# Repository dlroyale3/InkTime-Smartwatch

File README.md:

# Proiect InkTime - E-Paper Smartwatch (nRF52840)

## Descriere Generală
InkTime este un prototip hardware de smartwatch (dispozitiv wearable) proiectat de la zero, cu un focus absolut pe eficiența energetică (Ultra-Low Power) și miniaturizare. 
Creierul sistemului este SoC-ul **Nordic nRF52840**, capabil de conectivitate Bluetooth 5.0 LE. Dispozitivul interacționează cu utilizatorul printr-un ecran E-Paper de 3.3V (tehnologie bistabilă), butoane tactile și feedback haptic (motor liniar/ERM), fiind capabil să monitorizeze activitatea fizică prin intermediul unui accelerometru integrat.

---

## 1. Diagramă Bloc

Arhitectura hardware este centrată în jurul microcontrolerului, care acționează ca un Master I2C/SPI pentru toate perifericele, permițând controlul granular al stărilor de alimentare pentru fiecare modul în parte.

---

## 2. Bill of Materials (BOM) - Componente Principale

Pentru producția și asamblarea PCB-ului (PCBA), componentele au fost selectate pe baza disponibilității la producătorul JLCPCB (LCSC Parts) și a footprint-ului redus (QFN, BGA sau 0402/0201 pentru pasive).

| Componentă (Designator) | Rol în Sistem | Producător | Datasheet | Link JLCPCB |
| :--- | :--- | :--- | :--- | :--- |
| **nRF52840-QIAA** (U1) | Microcontroller & BLE Radio | Nordic Semi | [Datasheet](https://infocenter.nordicsemi.com/pdf/nRF52840_PS_v1.7.pdf) | [C145322](https://jlcpcb.com/partdetail/NordicSemicon-nRF52840QIAAR/C145322) |
| **BQ25180YBGR** (IC1) | LiPo Battery Charger | Texas Instruments | [Datasheet](https://www.ti.com/lit/ds/symlink/bq25180.pdf) | [C3166611](https://jlcpcb.com/partdetail/TexasInstruments-BQ25180YBGR/C3166611) |
| **MAX17048G+T10** (U3) | Fuel Gauge (Monitor Baterie) | Analog Devices | [Datasheet](https://www.analog.com/media/en/technical-documentation/data-sheets/MAX17048-MAX17049.pdf) | [C82806](https://jlcpcb.com/partdetail/Maxim_Integrated-MAX17048GT10/C82806) |
| **RT6160AWSC** (IC9) | DC/DC Buck-Boost Converter | Richtek | [Datasheet](https://www.richtek.com/assets/product_file/RT6160A/DS6160A-02.pdf) | [C2834316](https://jlcpcb.com/parts) |
| **BMA423 / BMA421** (IC3) | Accelerometru Triaxial (IMU) | Bosch Sensortec | [Datasheet](https://www.bosch-sensortec.com/media/boschsensortec/downloads/datasheets/bst-bma423-ds004.pdf) | [C283838](https://jlcpcb.com/partdetail/BoschSensortec-BMA423/C283838) |
| **DRV2605YZFR** (IC2) | Haptic Driver (LRA/ERM) | Texas Instruments | [Datasheet](https://www.ti.com/lit/ds/symlink/drv2605.pdf) | [C74431](https://jlcpcb.com/partdetail/TexasInstruments-DRV2605YZFR/C74431) |
| **2450AT18B100E** (ANT1)| Antenă Ceramică 2.4 GHz | Johanson Tech | [Datasheet](https://www.johansontechnology.com/datasheets/2450AT18B100/2450AT18B100.pdf) | [C210086](https://jlcpcb.com/partdetail/JohansonTechnology-2450AT18B100E/C210086) |

*(Notă: Componentele pasive - rezistențe și condensatori de 0201/0402, inductoarele de putere și conectorii USB-C/FPC se regăsesc detaliate în fișierul `BOM.csv` din folderul Manufacturing).*

---

## 3. Funcționalitate Hardware Detaliată

Sistemul a fost împărțit în mai multe subsisteme, optimizate pentru a permite oprirea alimentării (Power Gating) atunci când nu sunt utilizate.

### 3.1. Procesare și Radio (nRF52840)
MCU-ul rulează la o tensiune stabilizată de 3.3V. Pentru a menține timing-ul BLE și RTC-ul (Real Time Clock) cu un consum de doar ~1.5µA, a fost integrat un cristal extern de 32.768 kHz (`X2`). Conexiunea radio se face printr-o rețea Pi-Matching către antena ceramică de 2.4GHz.

### 3.2. Magistrala I2C și Senzorii
Toate perifericele de monitorizare și input folosesc o magistrală comună **I2C** (Fast Mode - 400kHz), echipată cu rezistențe de pull-up de 10kΩ.
* **BMA423 (IMU - 0x18):** Configurabil să ruleze algoritmul de *step-counting* intern. Nu ține MCU-ul treaz; trimite un semnal pe pinul `IMU_INT1` doar când detectează pași sau gesturi (Tilt-to-Wake).
* **MAX17048 (Fuel Gauge - 0x36):** Estimează starea bateriei (State of Charge) fără a necesita o rezistență de șunt (care ar irosi energie), folosind algoritmul ModelGauge. Poate genera o alertă hardware (`ALERT`) când bateria scade sub un prag definit.
* **BQ25180 (Charger - 0x6A):** Negociază curentul de încărcare tras din portul USB-C (limitat software la 100mA - 300mA pentru a proteja celula LiPo mică).
* **DRV2605 (Haptic - 0x5A):** Conține o bibliotecă internă de forme de undă pentru vibrații. Este ținut în shutdown (consum <1µA) și activat doar la notificări prin pinul `HAPTIC_EN`.

### 3.3. Display-ul E-Paper (SPI)
Interfața vizuală folosește un panou bistabil conectat printr-un cablu FPC 24-pin.
* **Comunicația:** Se face via **SPI 4-wire** (doar TX/MOSI, deoarece ecranul nu trimite date înapoi, ci folosește un pin dedicat `EPD_BUSY` pentru a semnaliza starea).
* **Boost Circuit:** Deoarece cerneala electronică necesită tensiuni mari (VGH, VGL, +/- 15V) pentru a muta pigmenții, placa include circuitul de switching cu inductor de 68uH și diode Schottky MBR0530. Acest circuit este pornit exclusiv în secunda în care ecranul își dă refresh.

### 3.4. Calcule de Consum de Energie (Power Budget)
Eficiența proiectului se bazează pe regimul de funcționare *Duty-Cycled*. Estimarea autonomiei cu o baterie LiPo de **150 mAh**:

1. **Modul Deep Sleep (98% din timp):**
   * nRF52840 (System ON, RTC): ~1.5 µA
   * BMA423 (Low-power sensing): ~4 µA
   * BQ25180 + RT6160 (Quiescent): ~8 µA
   * Fuel Gauge (Hibernate): ~3 µA
   * Ecran E-Paper: 0 µA
   * **Total Sleep:** **~16.5 µA**

2. **Modul Activ (Evenimente periodice):**
   * Refresh Ecran (1 dată pe minut): ~8 mA timp de 1s.
   * Transmisie BLE: ~5 mA timp de 10ms.
   * **Consum Mediu Echivalent:** **~1.2 mA / oră** (incluzând spike-urile de refresh).

3. **Autonomie Teoretică:** `150 mAh / 1.2 mA ≈ 125 de ore (aprox. 5 zile)` de utilizare normală, cu potențial de extindere până la **săptămâni** dacă ecranul este actualizat doar la cerere (button press).

---

## 4. Alocarea Pinilor nRF52840 și Justificare

Rutarea pinilor (Pin Muxing) a fost aleasă strategic pentru a evita încrucișările pe PCB și pentru a grupa interfețele de mare viteză.

| Pin MCU | Funcție Atribuită | Tip Interfață | Justificarea Alegerii (Hardware Design) |
| :--- | :--- | :--- | :--- |
| **P0.00 / P0.01** | `XL1` / `XL2` | Analog | Pini dedicați hardware exclusiv pentru cristalul LFXO (32.768kHz). |
| **P0.06 / P0.07** | `SDA` / `SCL` | I2C (TWIM) | Plasați convenabil pe latura de jos a IC-ului, rutare directă spre grupul de senzori (Bottom). |
| **P0.08 / P1.08** | `IMU_INT1` / `IMU_INT2`| GPIO (Interrupt) | Intrări cu capacitate de *Wake-up*, conectate direct la accelerometru. |
| **P0.02 / P0.03** | `SCK` / `MOSI` | SPI (SPIM) | Alocați pentru a minimiza distanța fizică a traseelor de mare viteză către conectorul FPC al ecranului (partea dreaptă a plăcii). |
| **P0.17** | `EPD_BUSY` | GPIO (Input) | Citește flag-ul de busy de la ecran. Permite MCU-ului să doarmă între comenzile SPI. |
| **P1.06** | `HAPTIC_EN` | GPIO (Output) | Semnal digital simplu (Enable) pentru a tăia alimentarea driverului de vibrații. |
| **P1.01 / P1.02 / P1.03** | `SW_UP/DN/ENT` | GPIO (Input) | Pini configurați cu rezistențe de pull-up interne/externe pentru debounce-ul mecanic al butoanelor. |
| **SWDIO / SWDCLK** | Debug / Flash | SWD | Pini hardwired pentru programarea via conectorul TC2030-IDC. |

---

## 5. Design Log & PCB Layout (4-Layer Stackup)

PCB-ul a fost proiectat pe 4 straturi pentru a asigura plane solide de referință (GND), necesare disipării termice și integrității semnalului RF. 
S-a implementat o matrice de **Via Stitching** în jurul secțiunii de radiofrecvență și un decupaj (Polygon Cutout) pe toate cele 4 straturi sub antena Johanson, pentru a preveni atenuarea undelor electromagnetice.

* **Layer 1 (Top):** Găzduiește toate componentele SMD, planul de masă (GND) primar și traseele critice de scurtă distanță.

* **Layer 2 (Route2 / Inner GND):** Strat intern dedicat exclusiv unui plan de masă continuu (Solid Ground Plane). Acesta oferă o cale de întoarcere curată și scurtă pentru curenți, esențială pentru ecranarea zgomotului (EMI) și performanța antenei.

* **Layer 3 (Route63 / Inner Power):** Strat intern dedicat rețelelor de distribuție a puterii (`3V3`, `VBUS`, `VBAT`, `VREG`). Traseele au o lățime minimă de 0.3mm pentru a menține o impedanță redusă și a preveni căderile de tensiune la solicitări tranzitorii.

* **Layer 4 (Bottom):** Utilizat preponderent pentru rutarea magistralelor de date (ex: `I2C`) și pentru realizarea conexiunilor lungi care ar fi aglomerat fața Top. Dispune, de asemenea, de propriul plan de masă auxiliar.

### Testabilitate și Producție
Placa dispune de **Test Pad-uri** dedicate pentru toate semnalele critice (`3V3`, `VBAT`, `SDA`, `SCL`, `SWDIO`), etichetate clar pe layer-ul de Silkscreen, permițând depanarea facilă cu osciloscopul sau analizorul logic după asamblare.
### Testabilitate și Producție
Placa dispune de **Test Pad-uri** dedicate pentru toate semnalele critice (`3V3`, `VBAT`, `SDA`, `SCL`, `SWDIO`), etichetate clar pe layer-ul de Silkscreen, permițând depanarea facilă cu osciloscopul sau analizorul logic după asamblare.

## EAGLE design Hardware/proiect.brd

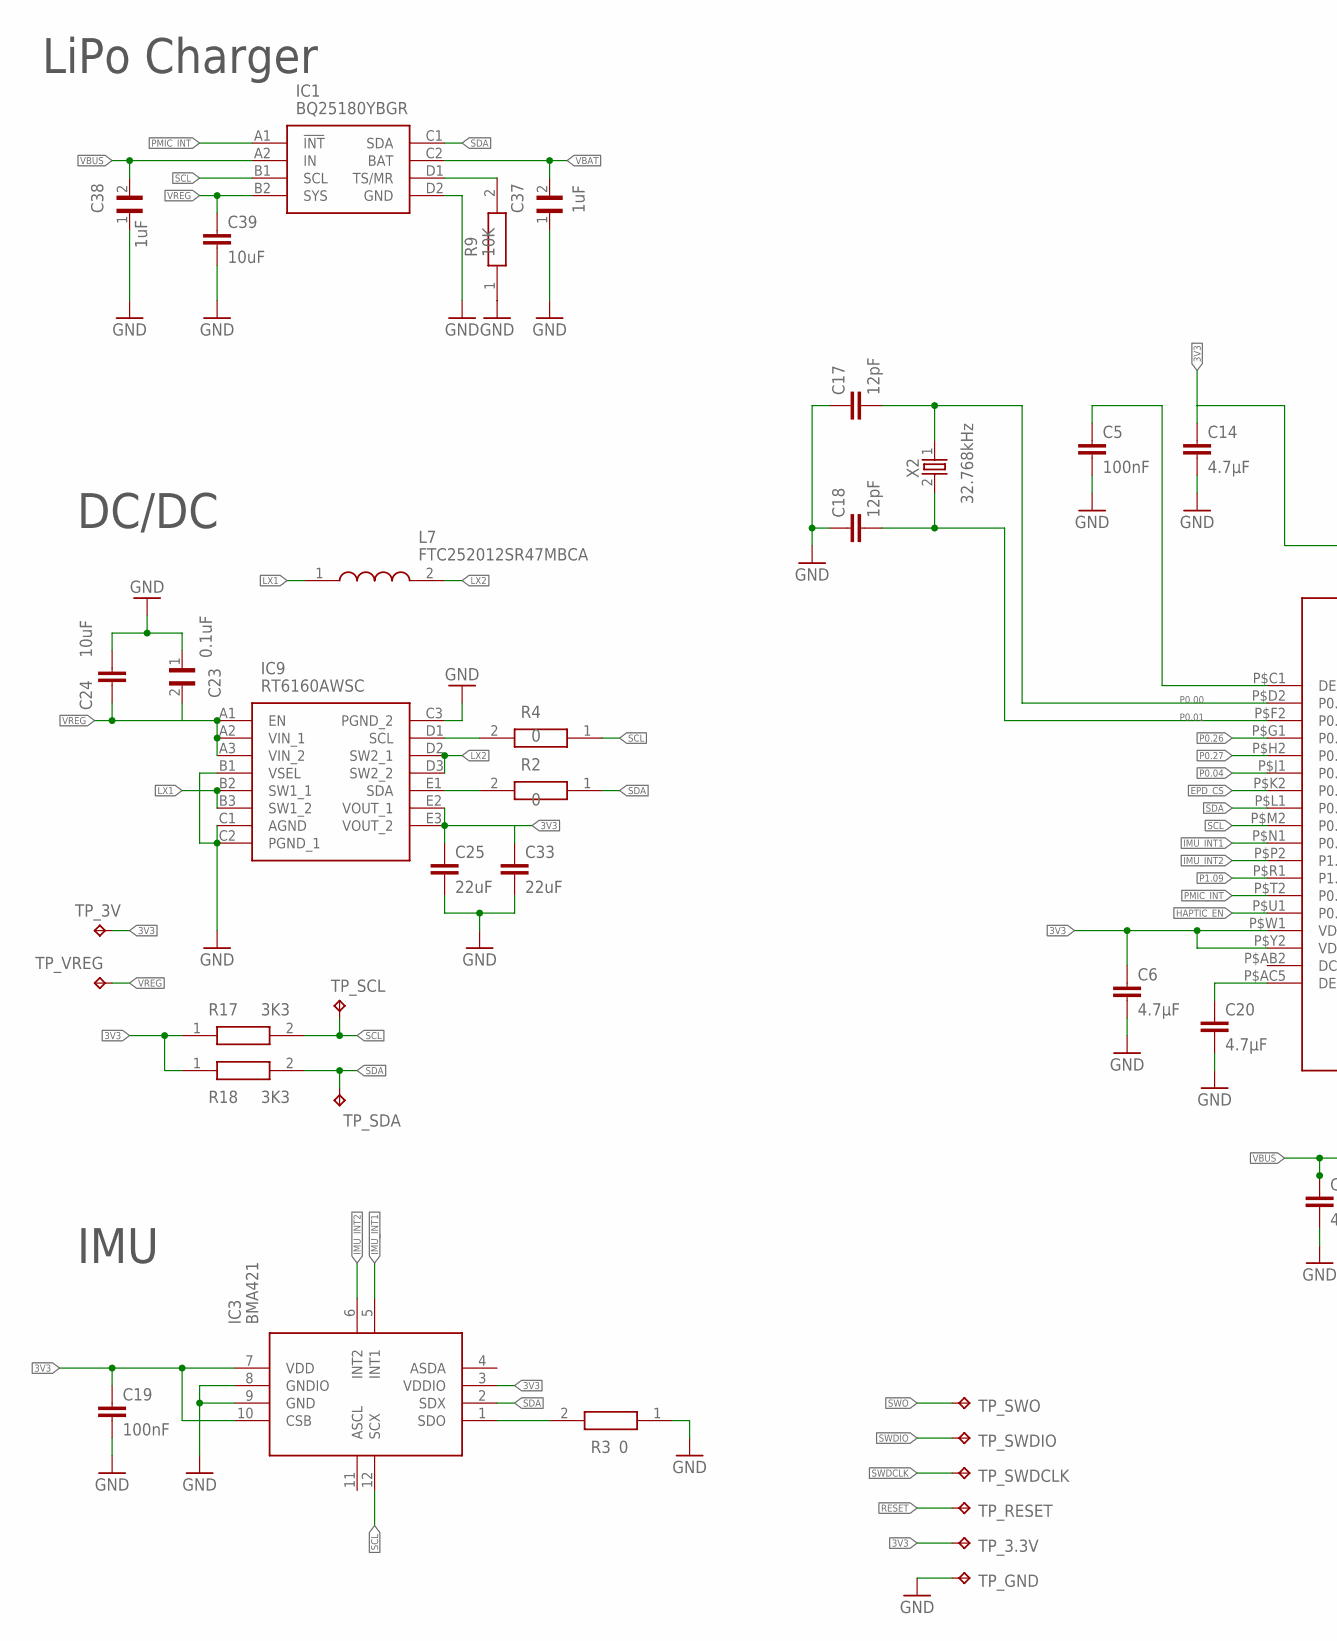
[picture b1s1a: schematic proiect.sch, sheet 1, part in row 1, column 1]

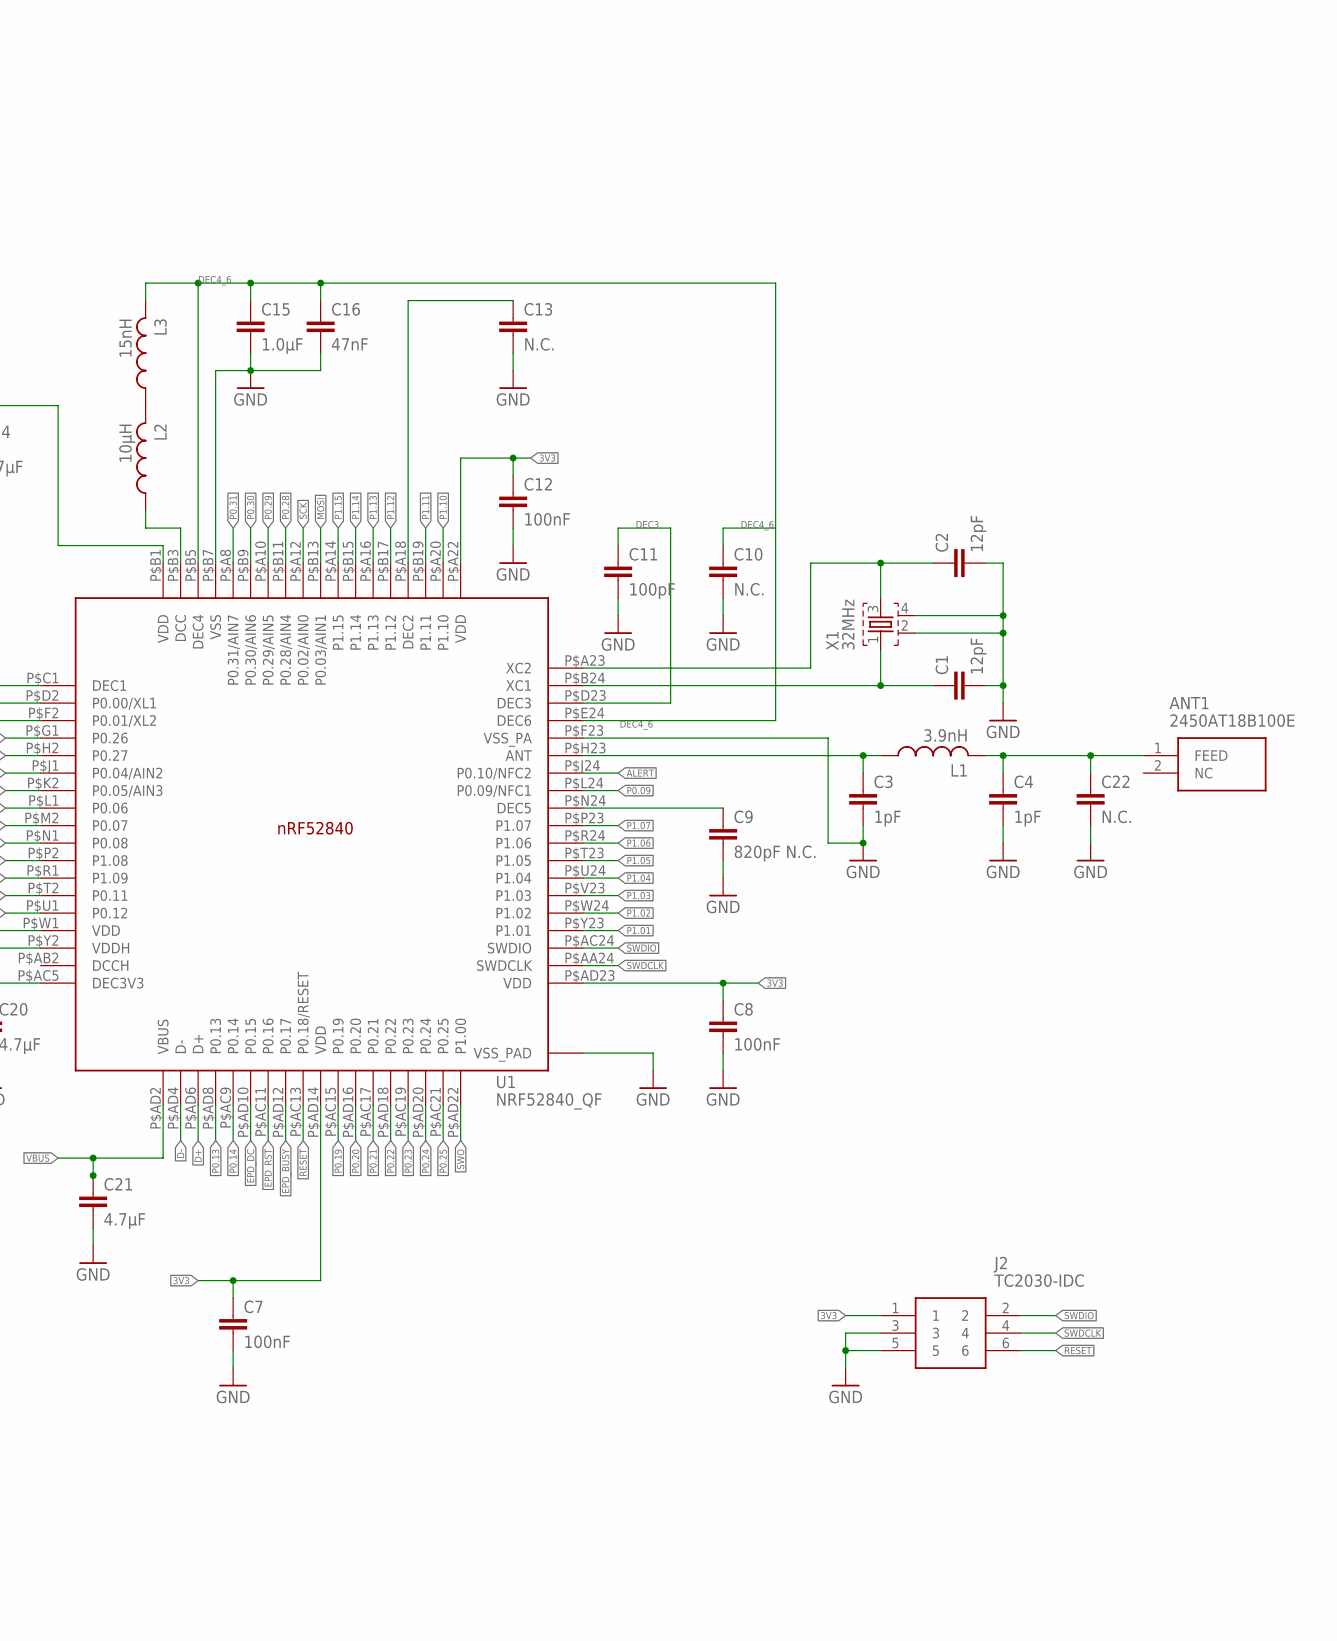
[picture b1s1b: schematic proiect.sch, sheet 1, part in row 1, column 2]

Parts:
ANT1: 2450AT18B100E; 2450AT18B100E_ANTC3216X140N
C1, C2, C17, C18: 12pF; NORDIC_NRF_3_RESC0201_L
C3, C4: 1pF; NORDIC_NRF_3_RESC0201_L
C5, C7, C8, C12, C19: 100nF; NORDIC_NRF_3_RESC0201_L
C6, C14, C20, C21: 4.7µF; NORDIC_NRF_3_RESC0201_L
C9: 820pF N.C.; NORDIC_NRF_3_RESC0201_L
C10, C13, C22: N.C.; NORDIC_NRF_3_RESC0201_L
C11: 100pF; NORDIC_NRF_3_RESC0201_L
C15: 1.0µF; NORDIC_NRF_3_RESC0201_L
C16: 47nF; NORDIC_NRF_3_RESC0201_L
C23: 0.1uF; GRM011R60J152KE01L_1_0201
C24, C39: 10uF; NORDIC_NRF_3_RESC0201_L
C25, C33: 22uF; NORDIC_NRF_3_RESC0201_L
C37, C38: 1uF; GRM011R60J152KE01L_1_0201
IC1: BQ25180YBGR; BQ25180YBGR_BGA8C40P2X4_100X155X50
IC3: BMA421; BMA423_BMA423
IC9: RT6160AWSC; RT6160AWSC_BGA15C40P3X5_140X230X60
J2: TC2030-IDC; TC2030-IDC_TC2030IDC
L1: 3.9nH; NORDIC_NRF_2_RESC0402_L
L2: 10µH; NORDIC_NRF_2_RESC0402_L
L3: 15nH; NORDIC_NRF_2_RESC0402_L
L7: FTC252012SR47MBCA; MLP2016SR47MT0S1_INDC2016X100N
R2, R3, R4: 0; CPF0201D7K68C1_0201
R9: 10K; CPF0201D7K68C1_0201
R17, R18: 3K3; CPF0201D7K68C1_0201
TP_3.3V, TP_3V: HECTOR_WATCH_1_TPTP20R; HECTOR_WATCH_1_TP20R
TP_GND: HECTOR_WATCH_1_TPTP20R; HECTOR_WATCH_1_TP20R
TP_RESET: HECTOR_WATCH_1_TPTP20R; HECTOR_WATCH_1_TP20R
TP_SCL: HECTOR_WATCH_1_TPTP20R; HECTOR_WATCH_1_TP20R
TP_SDA: HECTOR_WATCH_1_TPTP20R; HECTOR_WATCH_1_TP20R
TP_SWDCLK: HECTOR_WATCH_1_TPTP20R; HECTOR_WATCH_1_TP20R
TP_SWDIO: HECTOR_WATCH_1_TPTP20R; HECTOR_WATCH_1_TP20R
TP_SWO: HECTOR_WATCH_1_TPTP20R; HECTOR_WATCH_1_TP20R
TP_VREG: HECTOR_WATCH_1_TPTP20R; HECTOR_WATCH_1_TP20R
U1: NRF52840_QF; NORDIC_NRF_4_AQFN50P700X700X85_HS-74N
X1: 32MHz; NORDIC_NRF_BT-XTAL_2016_N
X2: 32.768kHz; NORDIC_NRF_1_XTAL_3215_N

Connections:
3V3: C6.1, C7.1, C8.1, C12.1, C14.1, C19.1, C25.1, IC3.3 (VDDIO), IC3.7 (VDD), IC3.10 (CSB), IC9.E2 (VOUT_1), IC9.E3 (VOUT_2), J2.1, R17.1, R18.1, TP_3.3V.TP, TP_3V.TP, U1.P$A22 (VDD), U1.P$AD14 (VDD), U1.P$AD23 (VDD), U1.P$B1 (VDD), U1.P$W1 (VDD), U1.P$Y2 (VDDH); also elsewhere on the board
ALERT: U1.P$J24 (P0.10/NFC2); also elsewhere on the board
D+: U1.P$AD6 (D+); also elsewhere on the board
D-: U1.P$AD4 (D-); also elsewhere on the board
DEC3: C11.1, U1.P$D23 (DEC3)
DEC4_6: C10.1, C15.1, C16.1, L3.2, U1.P$B5 (DEC4), U1.P$E24 (DEC6)
EPD_BUSY: U1.P$AD12 (P0.17); also elsewhere on the board
EPD_CS: U1.P$K2 (P0.05/AIN3); also elsewhere on the board
EPD_DC: U1.P$AD10 (P0.15); also elsewhere on the board
EPD_RST: U1.P$AC11 (P0.16); also elsewhere on the board
GND: C1.2, C2.2, C3.2, C4.2, C5.2, C6.2, C7.2, C8.2, C9.2, C10.2, C11.2, C12.2, C13.2, C14.2, C15.2, C16.2, C17.1, C18.1, C19.2, C20.2, C21.2, C22.2, C23.1, C24.1, C25.2, C33.2, C37.1, C38.1, C39.2, IC1.D2 (GND), IC3.8 (GNDIO), IC3.9 (GND), IC9.B1 (VSEL), IC9.C1 (AGND), IC9.C2 (PGND_1), IC9.C3 (PGND_2), J2.3, J2.5, R3.1, R9.1, TP_GND.TP, U1.P$74 (VSS_PAD), U1.P$75 (VSS_PAD), U1.P$76 (VSS_PAD), U1.P$77 (VSS_PAD), U1.P$78 (VSS_PAD), U1.P$79 (VSS_PAD), U1.P$80 (VSS_PAD), U1.P$81 (VSS_PAD), U1.P$82 (VSS_PAD), U1.P$83 (VSS_PAD), U1.P$84 (VSS_PAD), U1.P$85 (VSS_PAD), U1.P$86 (VSS_PAD), U1.P$87 (VSS_PAD), U1.P$88 (VSS_PAD), U1.P$89 (VSS_PAD), U1.P$90 (VSS_PAD), U1.P$B7 (VSS), U1.P$F23 (VSS_PA), X1.2, X1.4; also elsewhere on the board
HAPTIC_EN: U1.P$U1 (P0.12); also elsewhere on the board
IMU_INT1: IC3.5 (INT1), U1.P$N1 (P0.08)
IMU_INT2: IC3.6 (INT2), U1.P$P2 (P1.08)
LX1: IC9.B2 (SW1_1), IC9.B3 (SW1_2), L7.1
LX2: IC9.D2 (SW2_1), IC9.D3 (SW2_2), L7.2
MOSI: U1.P$B13 (P0.03/AIN1); also elsewhere on the board
unnamed: IC1.D1 (TS/MR), R9.2
unnamed: IC9.D1 (SCL), R4.2
unnamed: IC9.E1 (SDA), R2.2
unnamed: L2.2, L3.1
unnamed: L2.1, U1.P$B3 (DCC)
unnamed: C13.1, U1.P$A18 (DEC2)
unnamed: C5.1, U1.P$C1 (DEC1)
unnamed: C20.1, U1.P$AC5 (DEC3V3)
unnamed: C9.1, U1.P$N24 (DEC5)
unnamed: C3.1, L1.1, U1.P$H23 (ANT)
unnamed: ANT1.1 (FEED), C4.1, C22.1, L1.2
unnamed: C1.1, U1.P$B24 (XC1), X1.1
unnamed: C2.1, U1.P$A23 (XC2), X1.3
unnamed: IC3.1 (SDO), R3.2
P0.00: C17.2, U1.P$D2 (P0.00/XL1), X2.1
P0.01: C18.2, U1.P$F2 (P0.01/XL2), X2.2
P0.04: U1.P$J1 (P0.04/AIN2)
P0.09: U1.P$L24 (P0.09/NFC1)
P0.13: U1.P$AD8 (P0.13); also elsewhere on the board
P0.14: U1.P$AC9 (P0.14); also elsewhere on the board
P0.19: U1.P$AC15 (P0.19)
P0.20: U1.P$AD16 (P0.20)
P0.21: U1.P$AC17 (P0.21)
P0.22: U1.P$AD18 (P0.22)
P0.23: U1.P$AC19 (P0.23)
P0.24: U1.P$AD20 (P0.24)
P0.25: U1.P$AC21 (P0.25)
P0.26: U1.P$G1 (P0.26)
P0.27: U1.P$H2 (P0.27)
P0.28: U1.P$B11 (P0.28/AIN4)
P0.29: U1.P$A10 (P0.29/AIN5)
P0.30: U1.P$B9 (P0.30/AIN6)
P0.31: U1.P$A8 (P0.31/AIN7)
P1.01: U1.P$Y23 (P1.01); also elsewhere on the board
P1.02: U1.P$W24 (P1.02); also elsewhere on the board
P1.03: U1.P$V23 (P1.03)
P1.04: U1.P$U24 (P1.04)
P1.05: U1.P$T23 (P1.05)
P1.06: U1.P$R24 (P1.06)
P1.07: U1.P$P23 (P1.07)
P1.09: U1.P$R1 (P1.09)
P1.10: U1.P$A20 (P1.10)
P1.11: U1.P$B19 (P1.11)
P1.12: U1.P$B17 (P1.12)
P1.13: U1.P$A16 (P1.13)
P1.14: U1.P$B15 (P1.14)
P1.15: U1.P$A14 (P1.15)
PMIC_INT: IC1.A1 (!INT), U1.P$T2 (P0.11)
RESET: J2.6, TP_RESET.TP, U1.P$AC13 (P0.18/RESET)
SCK: U1.P$A12 (P0.02/AIN0); also elsewhere on the board
SCL: IC1.B1 (SCL), IC3.12 (SCX), R4.1, R17.2, TP_SCL.TP, U1.P$M2 (P0.07); also elsewhere on the board
SDA: IC1.C1 (SDA), IC3.2 (SDX), R2.1, R18.2, TP_SDA.TP, U1.P$L1 (P0.06); also elsewhere on the board
SWDCLK: J2.4, TP_SWDCLK.TP, U1.P$AA24 (SWDCLK)
SWDIO: J2.2, TP_SWDIO.TP, U1.P$AC24 (SWDIO)
SWO: TP_SWO.TP, U1.P$AD22 (P1.00)
VBAT: C37.2, IC1.C2 (BAT); also elsewhere on the board
VBUS: C21.1, C38.2, IC1.A2 (IN), U1.P$AD2 (VBUS); also elsewhere on the board
VREG: C23.2, C24.2, C39.1, IC1.B2 (SYS), IC9.A1 (EN), IC9.A2 (VIN_1), IC9.A3 (VIN_2), TP_VREG.TP

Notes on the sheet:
LiPo Charger
DC/DC
IMU

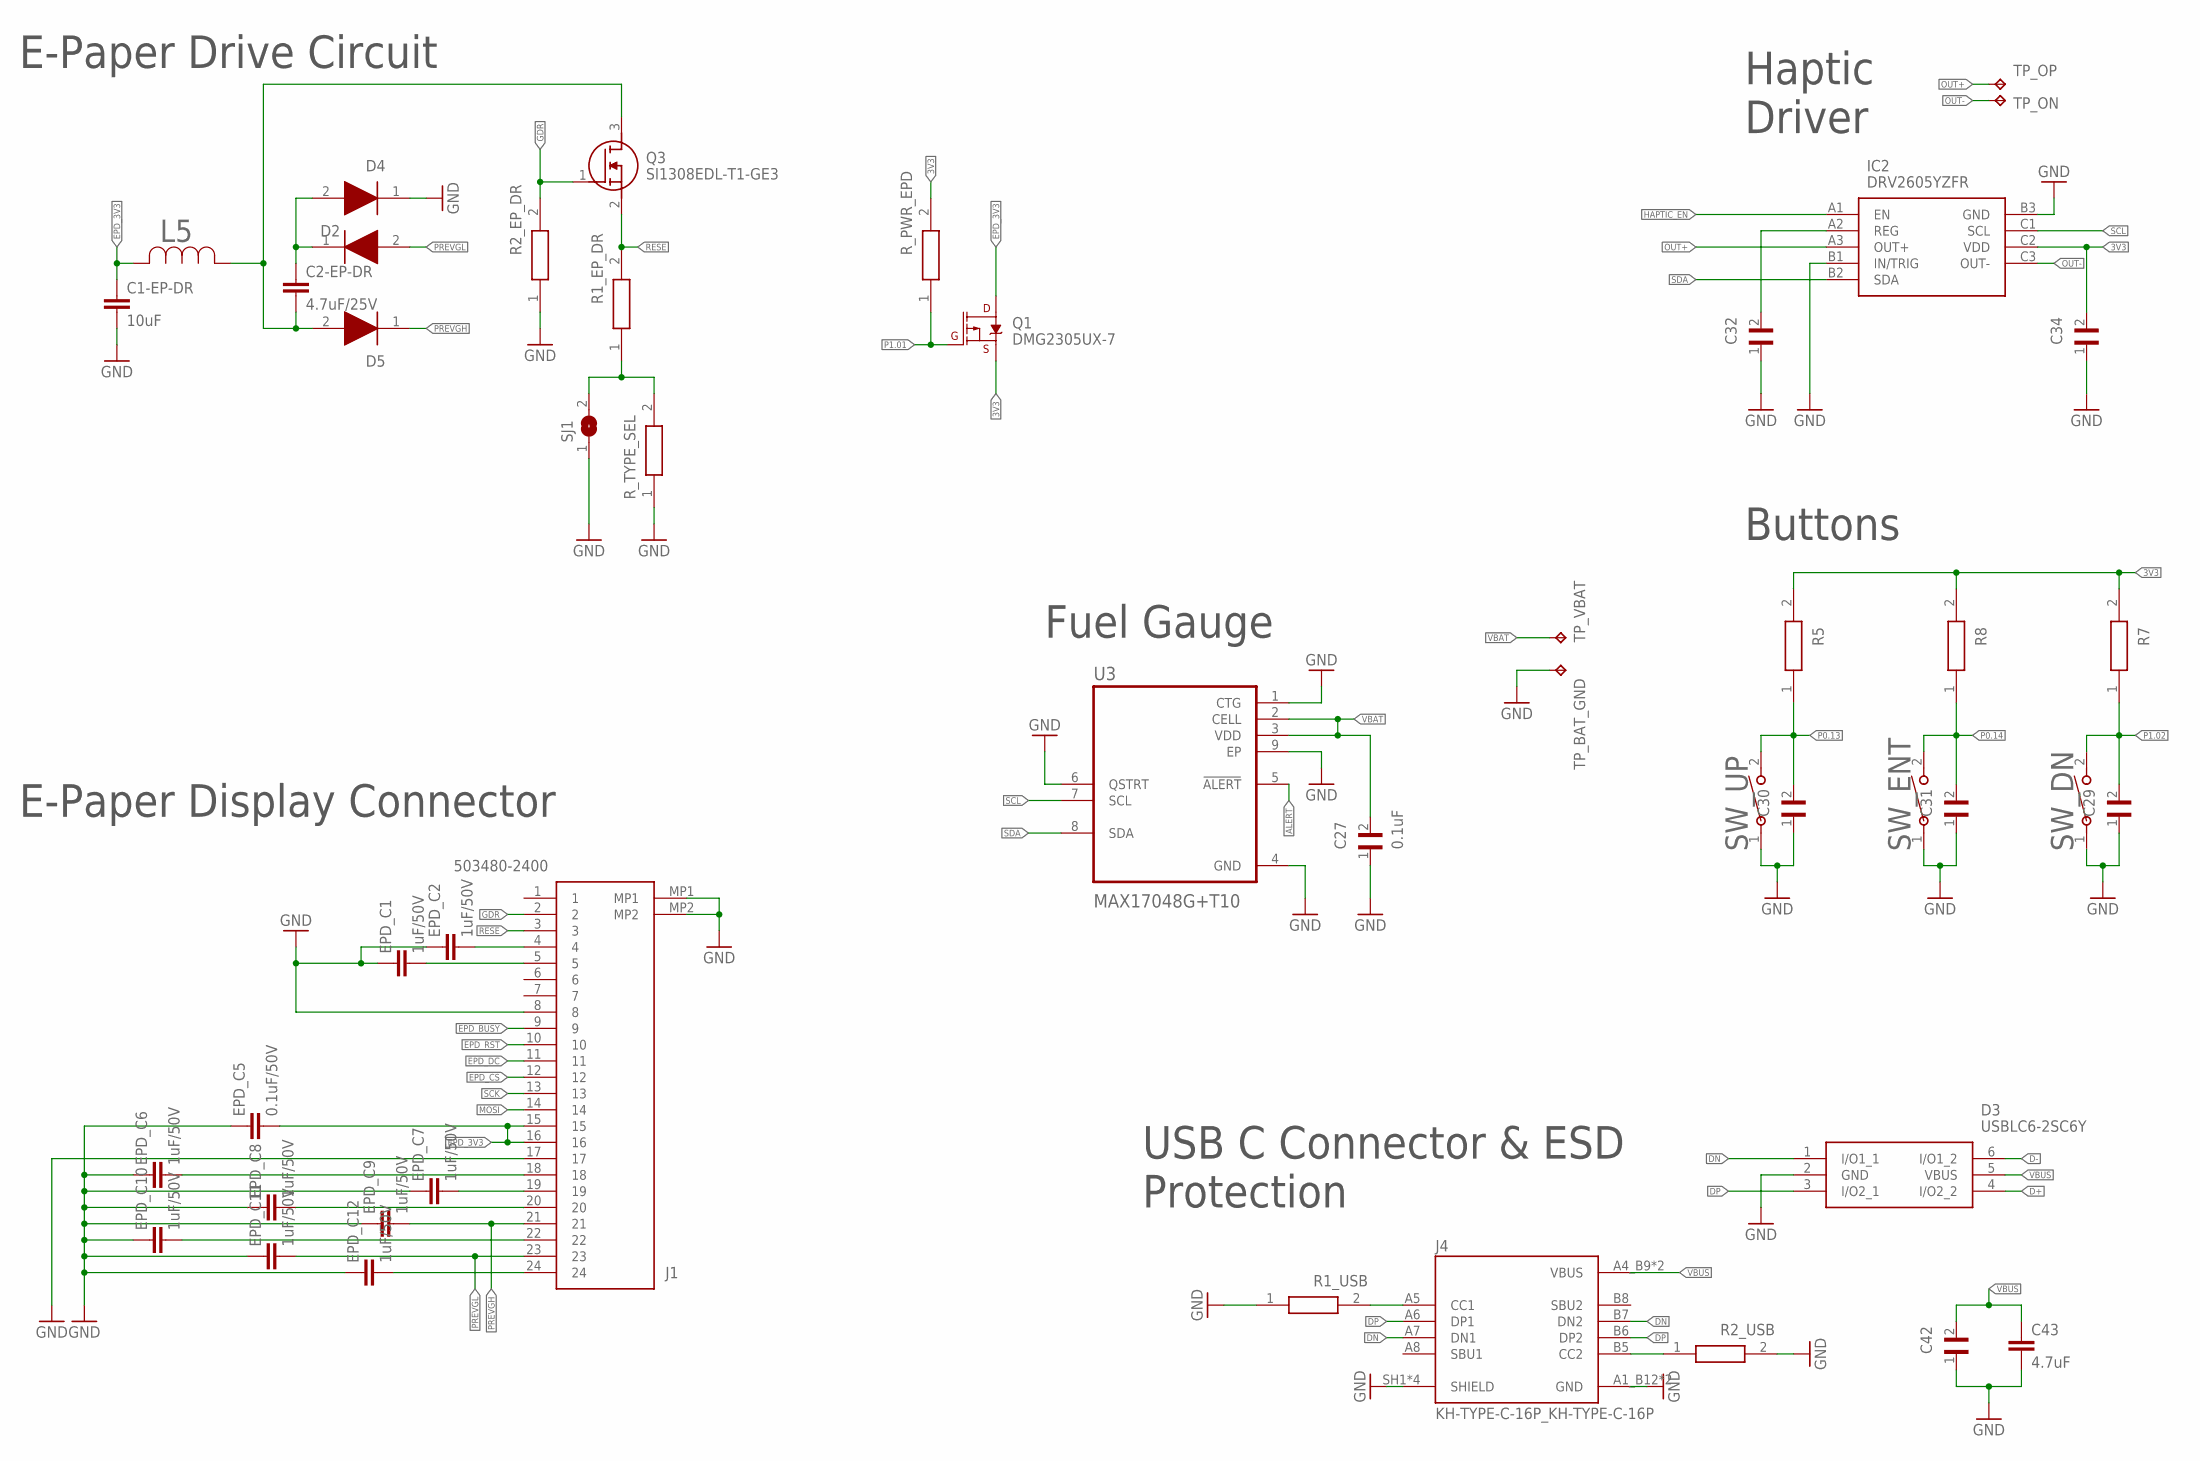
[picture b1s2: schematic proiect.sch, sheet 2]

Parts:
C1-EP-DR: 10uF; NORDIC_NRF_3_RESC0201_L
C2-EP-DR: 4.7uF/25V; NORDIC_NRF_3_RESC0201_L
C27, C34, C42: 0.1uF; GRM011R60J152KE01L_1_0201
C29, C30, C31, C32: 1uF; GRM011R60J152KE01L_1_0201
C43: 4.7uF; NORDIC_NRF_3_RESC0201_L
D2, D4, D5: ESP32_C6_LIBRARY_5_MBR0530; ESP32_C6_LIBRARY_5_SOD3716X135N
D3: USBLC6-2SC6Y; ESP32_C6_LIBRARY_3_SOT95P280X145-6N
EPD_C1, EPD_C2, EPD_C6, EPD_C7, EPD_C8, EPD_C9, EPD_C10, EPD_C11, EPD_C12: 1uF/50V; NORDIC_NRF_3_RESC0201_L
EPD_C5: 0.1uF/50V; NORDIC_NRF_3_RESC0201_L
IC2: DRV2605YZFR; DRV2605YZFR_BGA9C50P3X3_144X144X62
J1: 503480-2400; 503480-2400_5034802400
J4: KH-TYPE-C-16P_KH-TYPE-C-16P; KH-TYPE-C-16P_KINGHELM_KH-TYPE-C-16P
L5: ESP32_C6_LIBRARY_2_744043680IND_4828-WE-TPC_WRE; ESP32_C6_LIBRARY_2_IND_4828-WE-TPC_WRE
Q1: DMG2305UX-7; ESP32_C6_LIBRARY_4_ESP32_C6_LIBRARY_4_ESP32_C6_LIBRARY_4_ES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
Q3: SI1308EDL-T1-GE3; ESP32_C6_LIBRARY_6_SOT65P210X110-3N
R1_EP_DR: 0.47; CPF0201D7K68C1_0201
R1_USB, R2_USB: 5K1; CPF0201D7K68C1_0201
R2_EP_DR, R5, R7, R8: 10K; CPF0201D7K68C1_0201
R_PWR_EPD: 10K; CPF0201D7K68C1_0201
R_TYPE_SEL: 2.2; CPF0201D7K68C1_0201
SJ1: ESP32_C6_LIBRARY_7_JUMPER_SJ
SW_DN: 2025-10-22_07-23-44_LIBRARY_EVP-AKE31ASW_EVP-AKE3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; 2025-10-22_07-23-44_LIBRARY_SW_EVP-AKE31A_PAN
SW_ENT: 2025-10-22_07-23-44_LIBRARY_EVP-AKE31ASW_EVP-AKE3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; 2025-10-22_07-23-44_LIBRARY_SW_EVP-AKE31A_PAN
SW_UP: 2025-10-22_07-23-44_LIBRARY_EVP-AKE31ASW_EVP-AKE3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; 2025-10-22_07-23-44_LIBRARY_SW_EVP-AKE31A_PAN
TP_BAT_GND: HECTOR_WATCH_1_TPTP20R; HECTOR_WATCH_1_TP20R
TP_ON: HECTOR_WATCH_1_TPTP20R; HECTOR_WATCH_1_TP20R
TP_OP: HECTOR_WATCH_1_TPTP20R; HECTOR_WATCH_1_TP20R
TP_VBAT: HECTOR_WATCH_1_TPTP20R; HECTOR_WATCH_1_TP20R
U3: MAX17048G+T10; ESP32_C6_LIBRARY_SON50P200X200X80-9N

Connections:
3V3: C34.2, IC2.C2 (VDD), Q1.2 (S), R5.2, R7.2, R8.2, R_PWR_EPD.2; also elsewhere on the board
ALERT: U3.5 (!ALERT); also elsewhere on the board
D+: D3.4 (I/O2_2); also elsewhere on the board
D-: D3.6 (I/O1_2); also elsewhere on the board
DN: D3.1 (I/O1_1), J4.A7 (DN1), J4.B7 (DN2)
DP: D3.3 (I/O2_1), J4.A6 (DP1), J4.B6 (DP2)
EPD_3V3: C1-EP-DR.1, EPD_C5.2, J1.15, J1.16, L5.2, Q1.3 (D)
EPD_BUSY: J1.9; also elsewhere on the board
EPD_CS: J1.12; also elsewhere on the board
EPD_DC: J1.11; also elsewhere on the board
EPD_RST: J1.10; also elsewhere on the board
GDR: J1.2, Q3.1 (G), R2_EP_DR.2
GND: C1-EP-DR.2, C27.1, C29.1, C30.1, C31.1, C32.1, C34.1, C42.1, C43.2, D3.2 (GND), D4.1 (K), EPD_C1.1, EPD_C2.1, EPD_C5.1, EPD_C6.1, EPD_C7.1, EPD_C8.1, EPD_C9.1, EPD_C10.1, EPD_C11.1, EPD_C12.1, IC2.B1 (IN/TRIG), IC2.B3 (GND), J1.8, J1.17, J1.MP1, J1.MP2, J4.A1_B12 (GND), J4.A12_B1 (GND), J4.SH1 (SHIELD), J4.SH2 (SHIELD), J4.SH3 (SHIELD), J4.SH4 (SHIELD), R1_USB.1, R2_EP_DR.1, R2_USB.2, R_TYPE_SEL.1, SJ1.1, SW_DN.1, SW_ENT.1, SW_UP.1, TP_BAT_GND.TP, U3.1 (CTG), U3.4 (GND), U3.6 (QSTRT), U3.9 (EP); also elsewhere on the board
HAPTIC_EN: IC2.A1 (EN); also elsewhere on the board
MOSI: J1.14; also elsewhere on the board
unnamed: C2-EP-DR.2, D5.2 (A), L5.1, Q3.3 (D)
unnamed: C2-EP-DR.1, D2.1 (K), D4.2 (A)
unnamed: R1_EP_DR.1, R_TYPE_SEL.2, SJ1.2
unnamed: EPD_C2.2, J1.4
unnamed: EPD_C1.2, J1.5
unnamed: EPD_C7.2, J1.19
unnamed: EPD_C12.2, J1.24
unnamed: EPD_C8.2, J1.20
unnamed: EPD_C6.2, J1.18
unnamed: EPD_C10.2, J1.22
unnamed: J4.A5 (CC1), R1_USB.2
unnamed: J4.B5 (CC2), R2_USB.1
unnamed: C32.2, IC2.A2 (REG)
OUT+: IC2.A3 (OUT+), TP_OP.TP
OUT-: IC2.C3 (OUT-), TP_ON.TP
P0.13: C30.2, R5.1, SW_UP.2; also elsewhere on the board
P0.14: C31.2, R8.1, SW_ENT.2; also elsewhere on the board
P1.01: Q1.1 (G), R_PWR_EPD.1; also elsewhere on the board
P1.02: C29.2, R7.1, SW_DN.2; also elsewhere on the board
PREVGH: D5.1 (K), EPD_C9.2, J1.21
PREVGL: D2.2 (A), EPD_C11.2, J1.23
RESE: J1.3, Q3.2 (S), R1_EP_DR.2
SCK: J1.13; also elsewhere on the board
SCL: IC2.C1 (SCL), U3.7 (SCL); also elsewhere on the board
SDA: IC2.B2 (SDA), U3.8 (SDA); also elsewhere on the board
VBAT: C27.2, TP_VBAT.TP, U3.2 (CELL), U3.3 (VDD); also elsewhere on the board
VBUS: C42.2, C43.1, D3.5 (VBUS), J4.A4_B9 (VBUS), J4.A9_B4 (VBUS); also elsewhere on the board

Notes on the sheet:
E-Paper Drive Circuit
E-Paper Display Connector
Fuel Gauge
USB C Connector & ESD Protection
Buttons
Haptic Driver

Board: 2 copper layers, 105 parts (0 on the bottom side), 70 nets, no tracks yet.

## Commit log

2026-04-16 Add files via upload
    Updated routing for PCB
2026-04-21 Revise README for InkTime E-Paper Smartwatch project
    Updated README with detailed project description, block diagram, BOM, hardware functionality, pin allocation, and PCB layout.
2026-04-21 Upload final release: Hardware, Manufacturing and 3D files

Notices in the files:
parts and their libraries:
COPYRIGHT: Copyright (C) 2024 Ultra Librarian. All rights reserved.
COPYRIGHT: Copyright (C) 2025 Ultra Librarian. All rights reserved.
